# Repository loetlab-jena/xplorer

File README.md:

xplorer
=======

Software for the balloon project "XPlorer 25"

fmmod
======

complex frequency modulator for i/q signal processing

Usage: fmmod inputfile outputfile [carrier] [freqdev] [gain]

             inputfile: path to input file(needs to be single channel)
             outputfile: path to output file
             carrier: carrier frequency in Hz(standard: 0.0)
             freqdev: frequency deviation in Hz(standard: 3000)
             gain: factor for amplification of modulated signal(0.0 < gain < 1.0)

command for compiling:

make fmmod

missionctl
==========

connects the various modules to implement the actual mission schedule. it takes pictures from the camera, 
converts them to the format used by sstv, generates the SSTV and APRS signals, controls the release etc

transmitter
===========

implements a workqueue on the raspberry pi for files to send. with this logic, missionctl doesn't have to keep track
on transmitting files but instead just tells the workqueue to send a file as soon as the RF is free

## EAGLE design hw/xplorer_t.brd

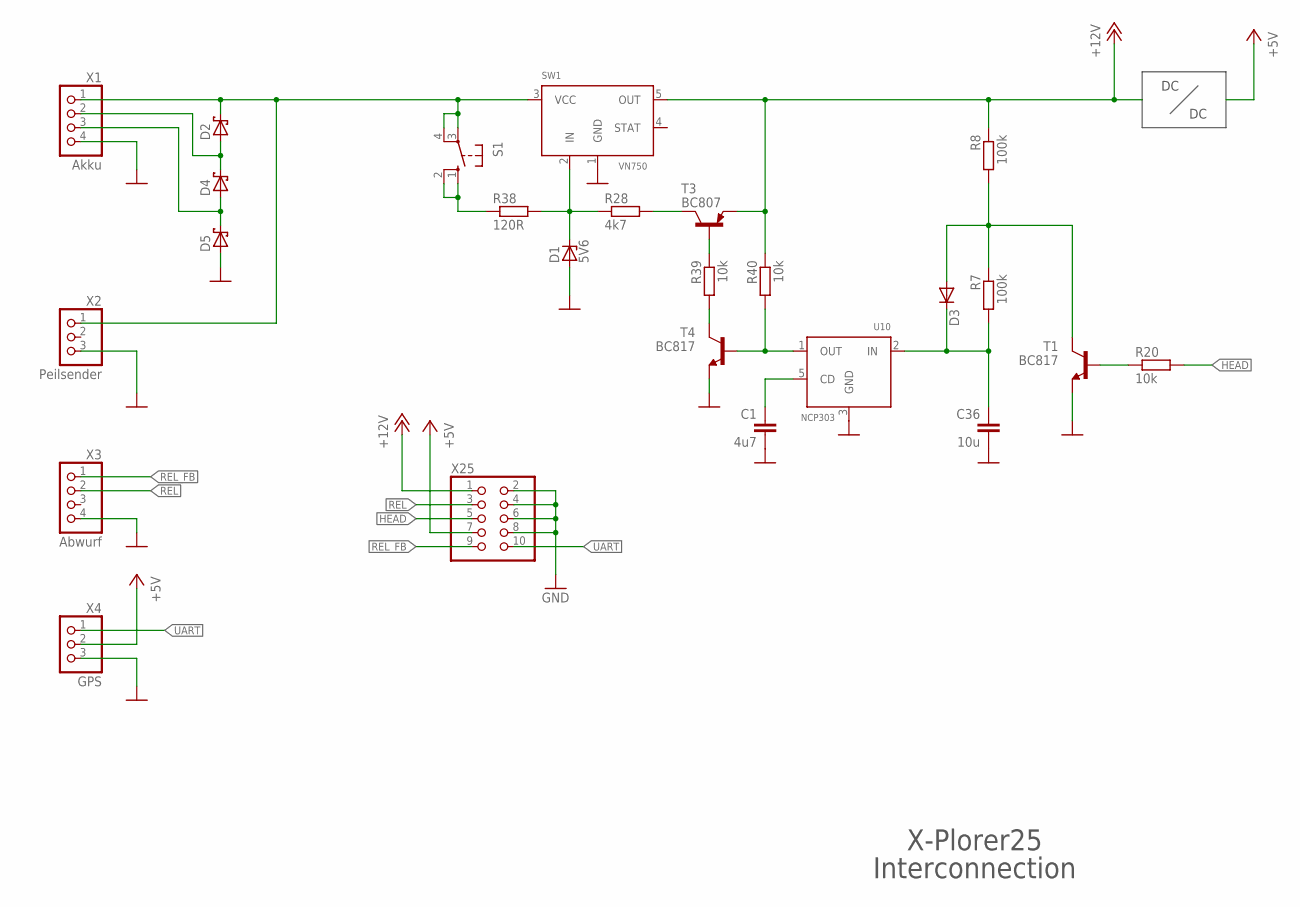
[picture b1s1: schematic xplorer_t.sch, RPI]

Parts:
C1: 4u7; C1210
C36: 10u; C1210
D1: 5V6; SOT23
D2, D4, D5: MBRS130LT3; SMB
D3: DIODE-MINIMELF; MINIMELF
R7, R8: 100k; R0805
R20, R39, R40: 10k; R0805
R28: 4k7; R0805
R38: 120R; R1206
S1: 10-XX; B3F-10XX
SW1: VN750; DDPAK
T1, T4: BC817; SOT23-BEC
T3: BC807; SOT23-BEC
U10: NCP303; SOT23-DBV
X1: Akku; 1X04
X2: Peilsender; 1X03/90
X3: Abwurf; 1X04/90
X4: GPS; 1X03
X25: PINHD-2X5; 2X05

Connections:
+5V: X4.2, X25.7
+12V: R8.1, R40.1, SW1.5 (OUT), T3.E, X25.1
GND: C1.2, C36.2, D1.1 (A), D5.A, SW1.1 (GND), T1.E, T4.E, U10.3 (GND), X1.4, X2.3, X3.4, X4.3, X25.2, X25.4, X25.6, X25.8
HEAD: R20.2, X25.5
unnamed: C1.1, U10.5 (CD)
unnamed: D2.A, D4.C, X1.2
unnamed: D4.A, D5.C, X1.3
unnamed: R38.1, S1.1 (S), S1.2 (S1)
unnamed: C36.1, D3.C, R7.2, U10.2 (IN)
unnamed: D2.C, S1.3, S1.4 (P1), SW1.3 (VCC), X1.1, X2.1
unnamed: D1.3 (C), R28.1, R38.2, SW1.2 (IN)
unnamed: D3.A, R7.1, R8.2, T1.C
unnamed: R28.2, T3.C
unnamed: R20.1, T1.B
unnamed: R39.2, T4.C
unnamed: R39.1, T3.B
unnamed: R40.2, T4.B, U10.1 (OUT)
REL: X3.2, X25.3
REL_FB: X3.1, X25.9
UART: X4.1, X25.10

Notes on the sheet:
X-Plorer25
Interconnection

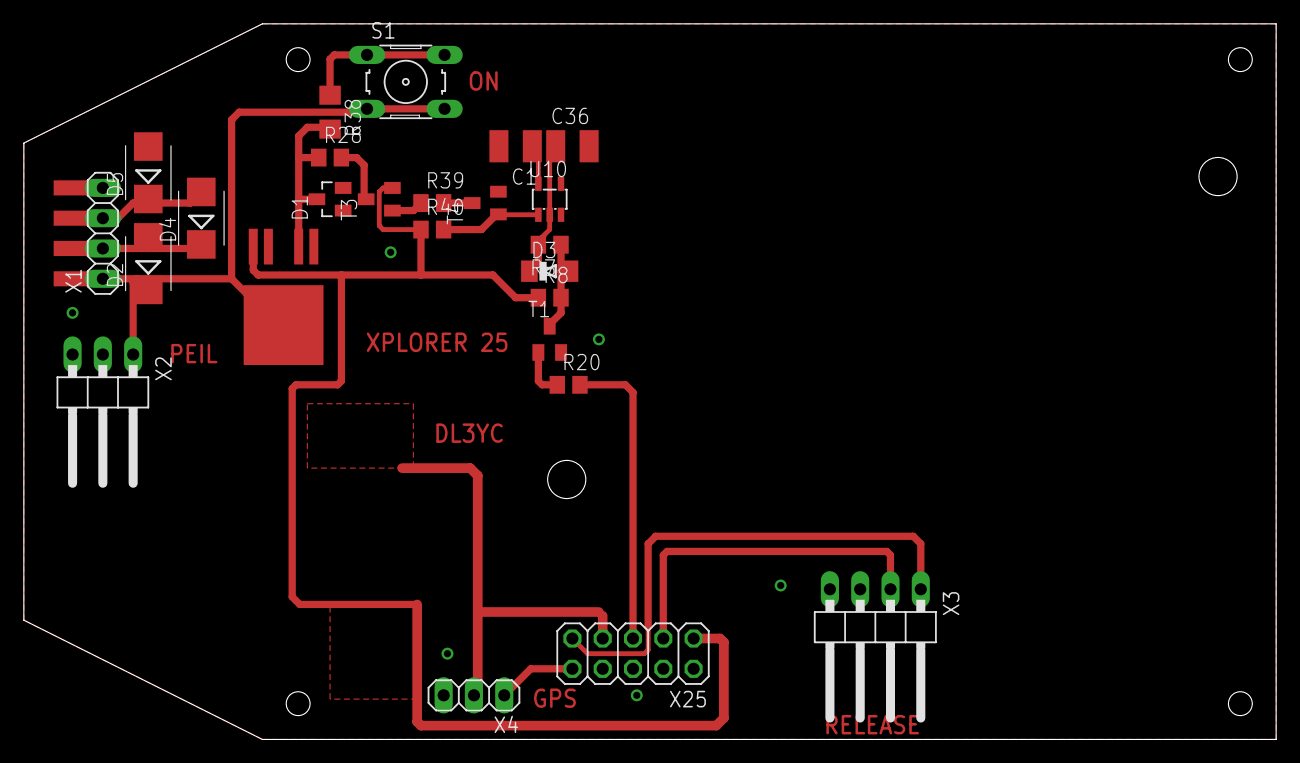
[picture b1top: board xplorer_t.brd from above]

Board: 2 copper layers, 105.0 x 60.0 mm, 25 parts (0 on the bottom side), 20 nets.

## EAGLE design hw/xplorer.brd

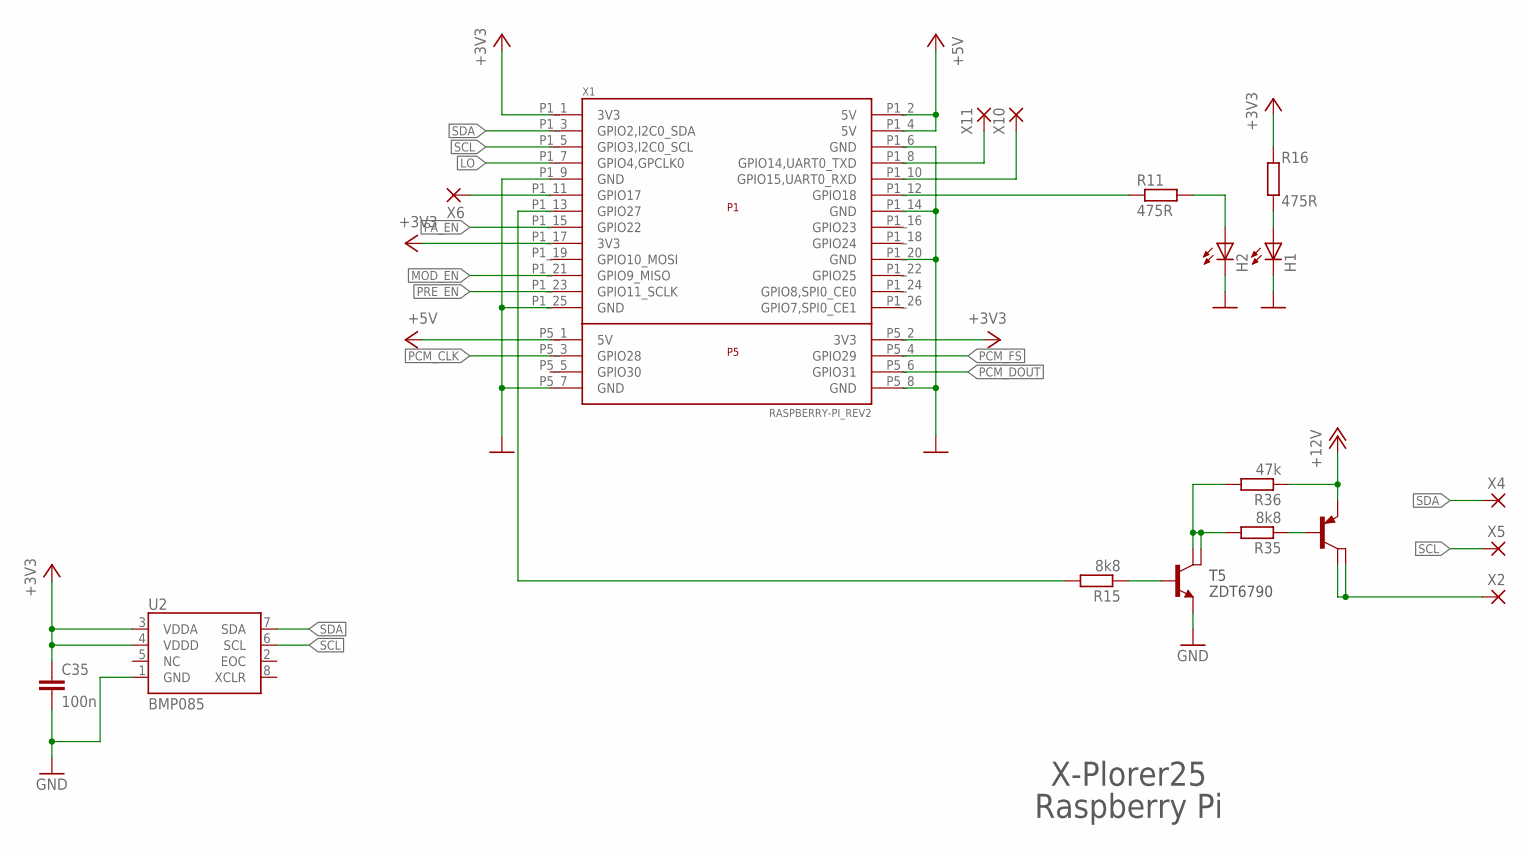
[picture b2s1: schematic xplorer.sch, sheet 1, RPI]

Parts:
C35: 100n; 0603
H1, H2: LEDCHIPLED_0603; CHIPLED_0603
R11, R16: 475R; R0402
R15, R35: 8k8; R0603
R36: 47k; R0603
T5: ZDT6790; SOT223-8
U2: BMP085
X1: RASPBERRY-PI_REV2
X2, X4, X5, X6, X10, X11: SMD2; SMD1,27-2,54

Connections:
$234567898765: T5.3 (C1), T5.4 (C2), X2.1
+3V3: C35.1, R16.2, U2.3 (VDDA), U2.4 (VDDD), X1.P1_1 (3V3), X1.P1_17 (3V3), X1.P5_2 (3V3)
+5V: X1.P1_2 (5V), X1.P1_4 (5V), X1.P5_1 (5V); also elsewhere on the board
+12V: R36.1, T5.5 (E); also elsewhere on the board
GND: C35.2, H1.C, H2.C, T5.7 (E), U2.1 (GND), X1.P1_6 (GND), X1.P1_9 (GND), X1.P1_14 (GND), X1.P1_20 (GND), X1.P1_25 (GND), X1.P5_7 (GND), X1.P5_8 (GND); also elsewhere on the board
LO: X1.P1_7 (GPIO4,GPCLK0); also elsewhere on the board
MOD_EN: X1.P1_21 (GPIO9_MISO); also elsewhere on the board
unnamed: H2.A, R11.2
unnamed: H1.A, R16.1
unnamed: X1.P1_10 (GPIO15,UART0_RXD), X10.1
unnamed: R11.1, X1.P1_12 (GPIO18)
unnamed: R15.1, T5.8 (B)
unnamed: R35.2, R36.2, T5.1 (C1), T5.2 (C2)
unnamed: R35.1, T5.6 (B)
unnamed: X1.P1_8 (GPIO14,UART0_TXD), X11.1
unnamed: R15.2, X1.P1_13 (GPIO27)
PA_EN: X1.P1_15 (GPIO22); also elsewhere on the board
PCM_CLK: X1.P5_3 (GPIO28); also elsewhere on the board
PCM_DOUT: X1.P5_6 (GPIO31); also elsewhere on the board
PCM_FS: X1.P5_4 (GPIO29); also elsewhere on the board
PRE_EN: X1.P1_23 (GPIO11_SCLK); also elsewhere on the board
REL_FB: X1.P1_11 (GPIO17), X6.1
SCL: U2.6 (SCL), X1.P1_5 (GPIO3,I2C0_SCL), X5.1
SDA: U2.7 (SDA), X1.P1_3 (GPIO2,I2C0_SDA), X4.1

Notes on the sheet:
X-Plorer25
Raspberry Pi
ZDT6790

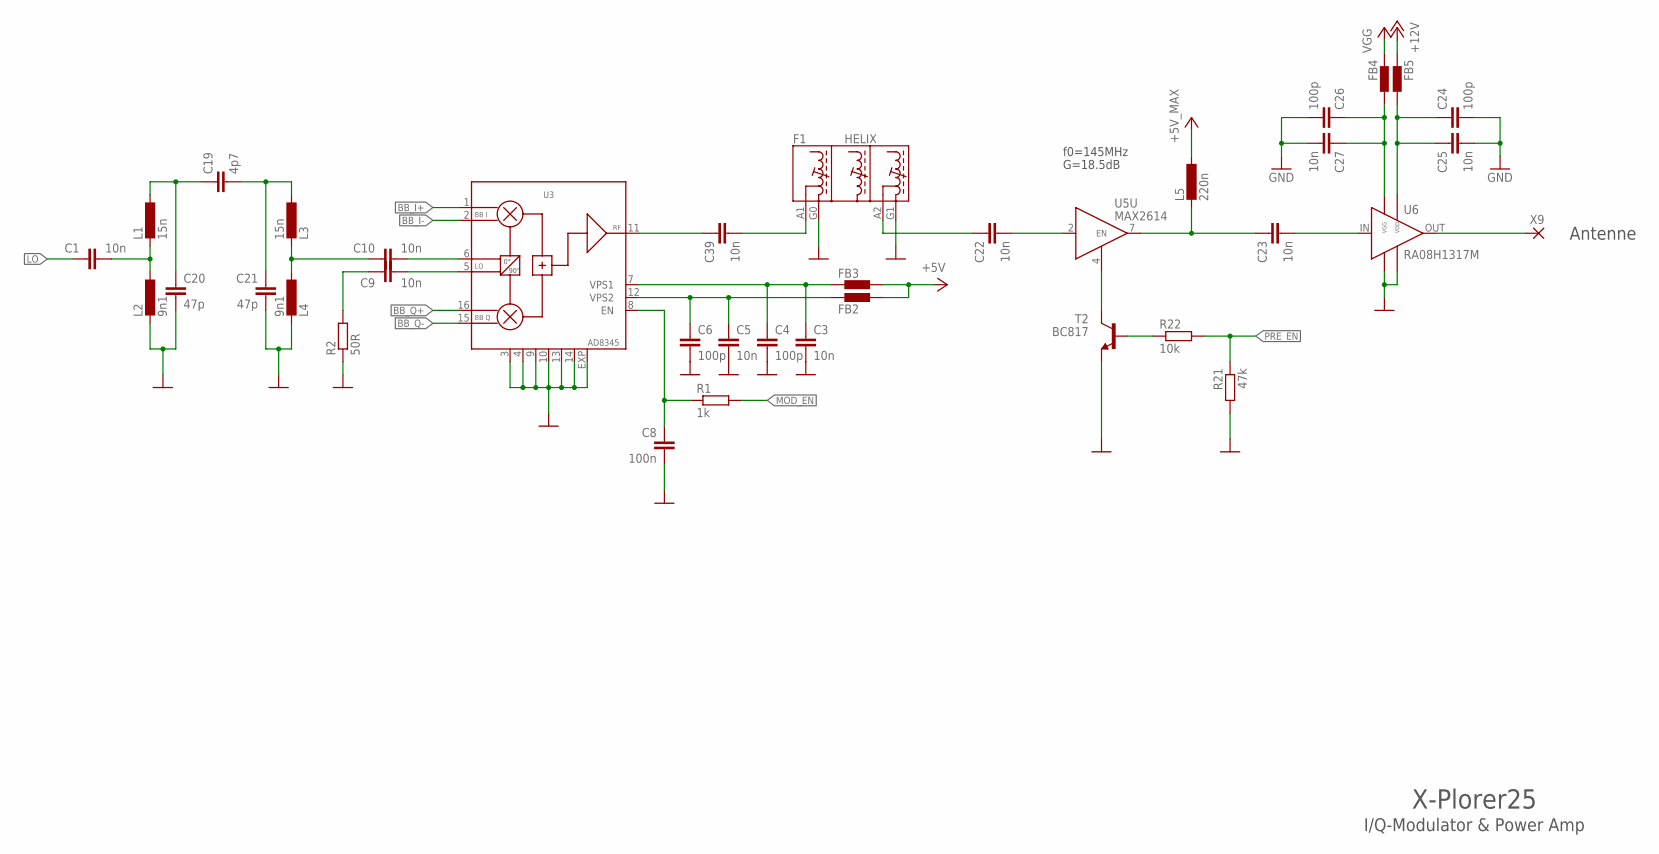
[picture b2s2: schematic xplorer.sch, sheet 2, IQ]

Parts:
C1, C3, C5, C9, C10, C22, C23, C25, C27, C39: 10n; C0603
C4, C6, C24, C26: 100p; C0603
C8: 100n; C0603
C19: 4p7; C0603
C20, C21: 47p; C1812
F1: HELIX; CBT13
FB2, FB3, FB4, FB5: BML15H; R0603
L1, L3: 15n; L2012C
L2, L4: 9n1; L2012C
L5: 220n; L2012C
R1: 1k; R0603
R2: 50R; R0603
R21: 47k; R0603
R22: 10k; R0603
T2: BC817; SOT23-BEC
U3: AD8345; TSSOP16EXP
U5: MAX2614; TDFN8-2X3MM
U6: RA08H1317M
X9: SMD2; SMD1,27-2,54

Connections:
+5V: FB2.2, FB3.2; also elsewhere on the board
+5V_MAX: L5.1; also elsewhere on the board
+12V: FB5.1; also elsewhere on the board
BB_I+: U3.1 (BB_I); also elsewhere on the board
BB_I-: U3.2 (!BB_I); also elsewhere on the board
BB_Q+: U3.16 (BB_Q); also elsewhere on the board
BB_Q-: U3.15 (!BB_Q); also elsewhere on the board
CLEAN_LO: C10.1, L3.2, L4.1
GND: C3.2, C4.2, C5.2, C6.2, C8.2, C20.2, C21.2, C24.2, C25.2, C26.2, C27.2, F1.G0 (GND), F1.G1 (GND), L2.2, L4.2, R2.1, R21.2, T2.E, U3.3 (GND), U3.4 (GND), U3.9 (GND), U3.10 (GND), U3.13 (GND), U3.14 (GND), U3.EXP (GND), U6.G1 (GND), U6.G2 (GND); also elsewhere on the board
LO: C1.1; also elsewhere on the board
MOD_EN: R1.2; also elsewhere on the board
unnamed: C39.2, F1.A1
unnamed: C10.2, U3.6 (LO)
unnamed: C3.1, C4.1, FB3.1, U3.7 (VPS1)
unnamed: C5.1, C6.1, FB2.1, U3.12 (VPS2)
unnamed: C8.1, R1.1, U3.8 (EN)
unnamed: C9.2, U3.5 (!LO)
unnamed: C9.1, R2.2
unnamed: C39.1, U3.11 (RF)
unnamed: C19.2, C21.1, L3.1
unnamed: C22.1, F1.A2
unnamed: C1.2, L1.2, L2.1
unnamed: C19.1, C20.1, L1.1
unnamed: C22.2, U5.2 (IN)
unnamed: C23.1, L5.2, U5.7 (OUT)
unnamed: C23.2, U6.IN
unnamed: C24.1, C25.1, FB5.2, U6.VDD
unnamed: C26.1, C27.1, FB4.2, U6.VGG
unnamed: U6.OUT, X9.1
unnamed: T2.C, U5.4 (EN)
unnamed: R22.1, T2.B
PRE_EN: R21.1, R22.2; also elsewhere on the board
VGG: FB4.1; also elsewhere on the board

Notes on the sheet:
X-Plorer25
I/Q-Modulator & Power Amp
f0=145MHz
G=18.5dB
Antenne

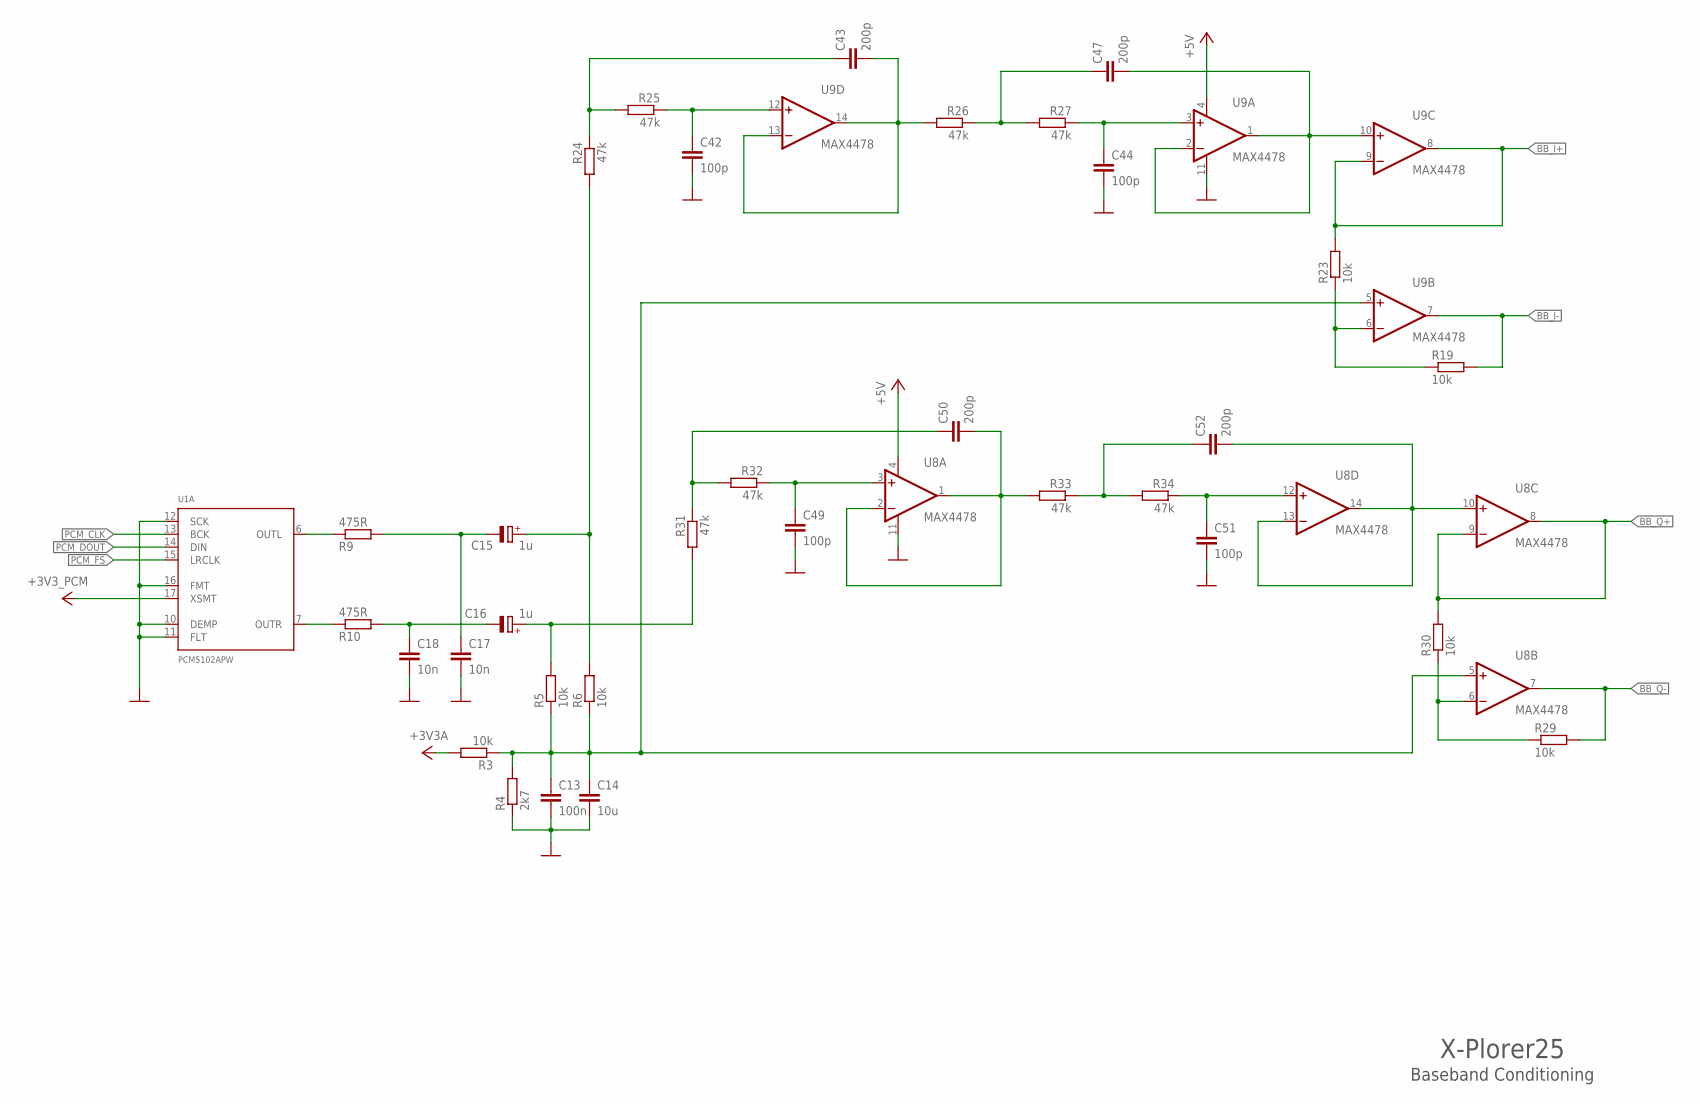
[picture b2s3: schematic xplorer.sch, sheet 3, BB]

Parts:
C13: 100n; C0603
C14: 10u; C0603
C15, C16: 1u; CT3528
C17, C18: 10n; C0603
C42, C44, C49, C51: 100p; C0603
C43, C47, C50, C52: 200p; C0805
R3, R5, R6, R19, R23, R29, R30: 10k; R0603
R4: 2k7; R0603
R9, R10: 475R; R0603
R24, R25, R26, R27, R31, R32, R33, R34: 47k; R0603
U1: PCM5102APW; PW_R-PDSO-G20
U8: MAX4478; SO14; MPN OPA4132UA
U9: MAX4478; SO14

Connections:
$2345: C16.+, R5.2, R31.2
$123456: C15.+, R6.2, R24.2
+3V3A: R3.2; also elsewhere on the board
+3V3_PCM: U1.17 (XSMT); also elsewhere on the board
+5V: U8.4 (V+), U9.4 (V+); also elsewhere on the board
BB_I+: R23.2, U9.8 (OUT), U9.9 (-IN); also elsewhere on the board
BB_I-: R19.2, U9.7 (OUT); also elsewhere on the board
BB_Q+: R30.2, U8.8 (OUT), U8.9 (-IN); also elsewhere on the board
BB_Q-: R29.2, U8.7 (OUT); also elsewhere on the board
GND: C13.2, C14.2, C17.2, C18.2, C42.2, C44.2, C49.2, C51.2, R4.1, U1.10 (DEMP), U1.11 (FLT), U1.12 (SCK), U1.16 (FMT), U8.11 (V-), U9.11 (V-); also elsewhere on the board
unnamed: C49.1, R32.1, U8.3 (+IN)
unnamed: R10.1, U1.7 (OUTR)
unnamed: C16.-, C18.1, R10.2
unnamed: R9.1, U1.6 (OUTL)
unnamed: C50.1, R31.1, R32.2
unnamed: C52.2, U8.10 (+IN), U8.13 (-IN), U8.14 (OUT)
unnamed: C51.1, R34.1, U8.12 (+IN)
unnamed: C52.1, R33.1, R34.2
unnamed: C42.1, R25.1, U9.12 (+IN)
unnamed: C43.1, R24.1, R25.2
unnamed: C47.2, U9.1 (OUT), U9.2 (-IN), U9.10 (+IN)
unnamed: C44.1, R27.1, U9.3 (+IN)
unnamed: C47.1, R26.1, R27.2
unnamed: C43.2, R26.2, U9.13 (-IN), U9.14 (OUT)
unnamed: C50.2, R33.2, U8.1 (OUT), U8.2 (-IN)
unnamed: R19.1, R23.1, U9.6 (-IN)
unnamed: R29.1, R30.1, U8.6 (-IN)
unnamed: C15.-, C17.1, R9.2
PCM_CLK: U1.13 (BCK); also elsewhere on the board
PCM_DOUT: U1.14 (DIN); also elsewhere on the board
PCM_FS: U1.15 (LRCLK); also elsewhere on the board
VGND: C13.1, C14.1, R3.1, R4.2, R5.1, R6.1, U8.5 (+IN), U9.5 (+IN)

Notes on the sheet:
X-Plorer25
Baseband Conditioning

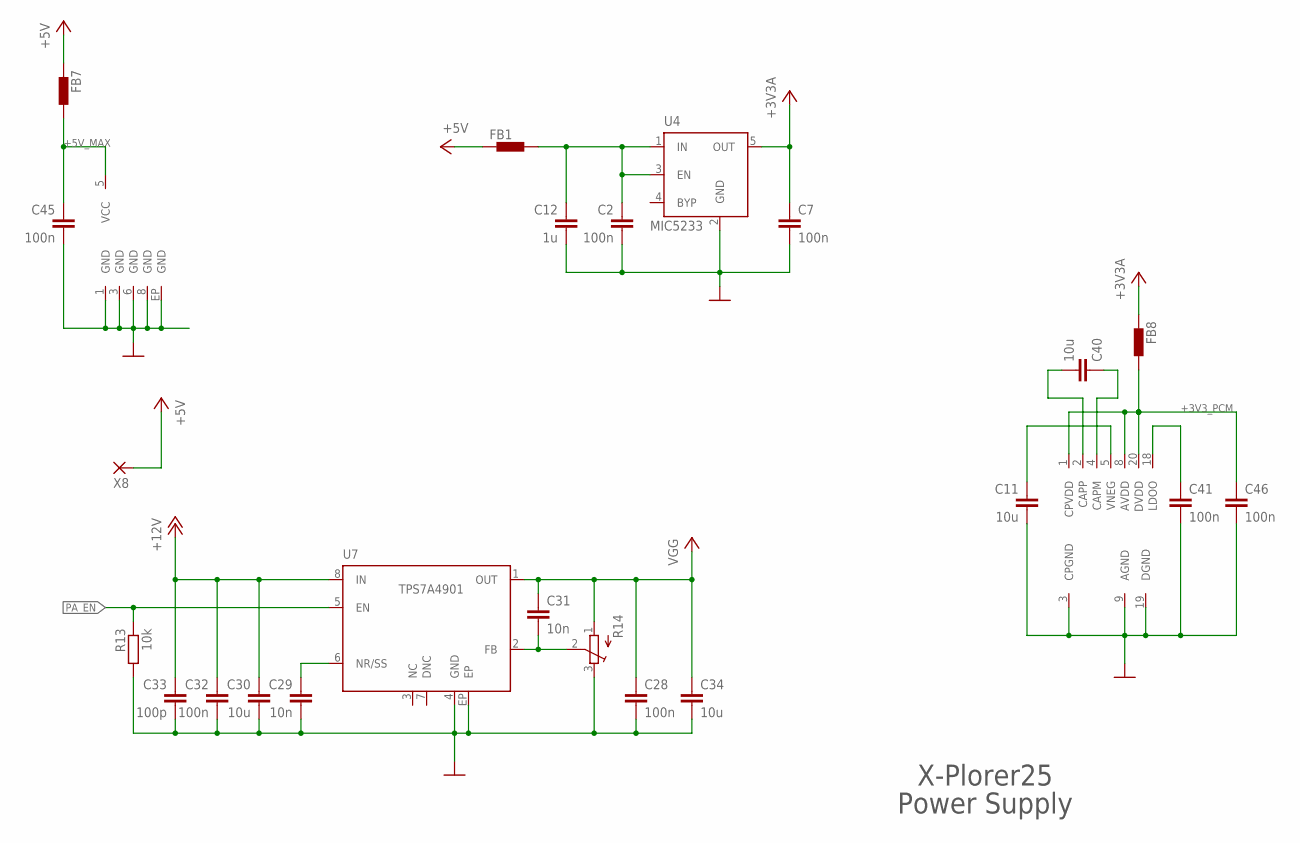
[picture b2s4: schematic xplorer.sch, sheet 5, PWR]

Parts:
C2, C7, C28, C32, C41, C45, C46: 100n; C0603
C11, C40: 10u; C0603
C12: 1u; C0603
C29: 10n; C0603K
C30, C34: 10u; C0805
C31: 10n; C0603
C33: 100p; C0603
FB1, FB7, FB8: BML15H; R0603
R13: 10k; R0603
R14: TRIM_EU-SM-42/43X; SM-42/43X
U1: PCM5102APW; PW_R-PDSO-G20
U4: MIC5233; SOT23-5
U5: MAX2614; TDFN8-2X3MM
U7: TPS7A4901; PW_R-PDSO-G08
X8: SMD2; SMD1,27-2,54

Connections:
12V_F: C2.1, C12.1, FB1.2, U4.1 (IN), U4.3 (EN)
+3V3A: C7.1, FB8.1, U4.5 (OUT); also elsewhere on the board
+3V3_PCM: C46.1, FB8.2, U1.1 (CPVDD), U1.8 (AVDD), U1.20 (DVDD); also elsewhere on the board
+5V: FB1.1, FB7.1, X8.1; also elsewhere on the board
+5V_MAX: C45.1, FB7.2, U5.5 (VCC); also elsewhere on the board
+12V: C30.1, C32.1, C33.1, U7.8 (IN); also elsewhere on the board
GND: C2.2, C7.2, C11.2, C12.2, C28.2, C29.2, C30.2, C32.2, C33.2, C34.2, C41.2, C45.2, C46.2, R13.2, R14.3 (E), U1.3 (CPGND), U1.9 (AGND), U1.19 (DGND), U4.2 (GND), U5.1 (GND), U5.3 (GND), U5.6 (GND), U5.8 (GND), U5.EP (GND), U7.4 (GND), U7.EP; also elsewhere on the board
unnamed: C31.2, R14.2 (S), U7.2 (FB)
unnamed: C11.1, U1.5 (VNEG)
unnamed: C40.1, U1.4 (CAPM)
unnamed: C40.2, U1.2 (CAPP)
unnamed: C41.1, U1.18 (LDOO)
unnamed: C29.1, U7.6 (NR/SS)
PA_EN: R13.1, U7.5 (EN); also elsewhere on the board
VGG: C28.1, C31.1, C34.1, R14.1 (A), U7.1 (OUT); also elsewhere on the board

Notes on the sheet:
X-Plorer25
Power Supply

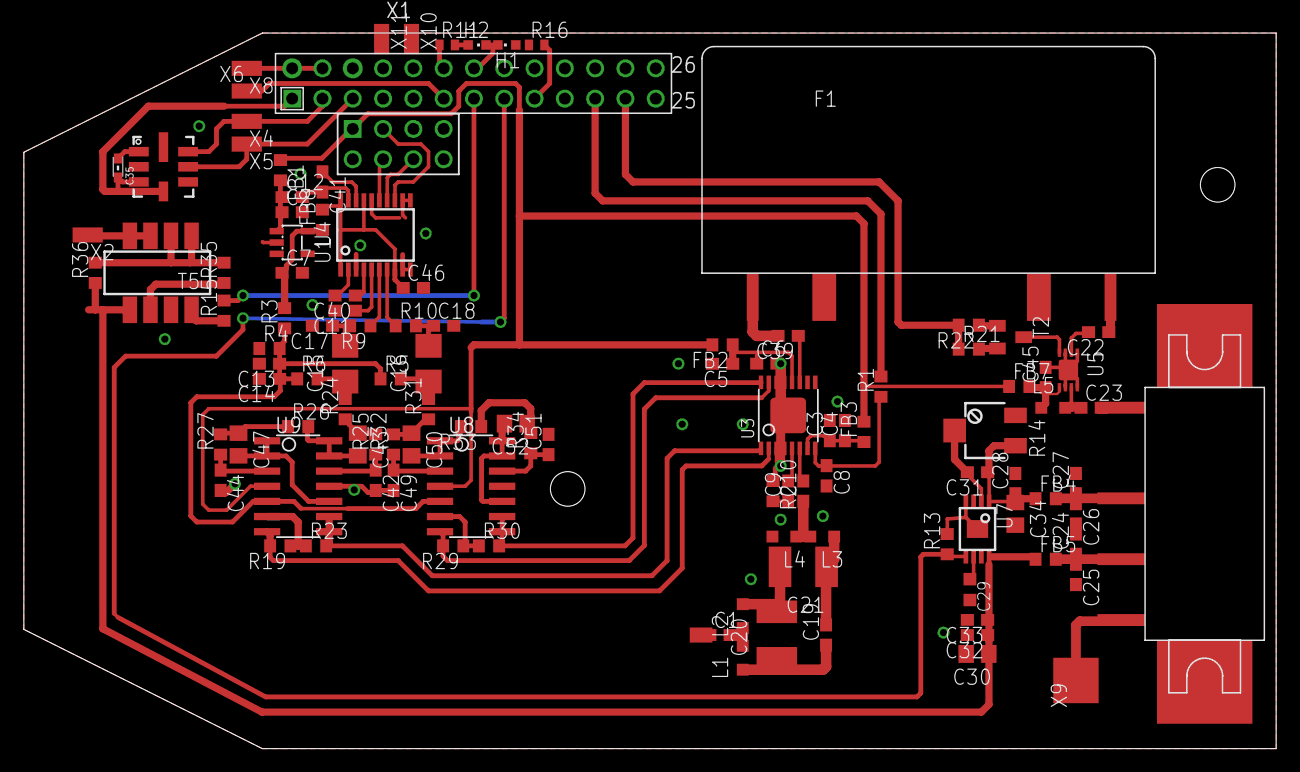
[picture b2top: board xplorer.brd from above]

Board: 2 copper layers, 105.0 x 60.0 mm, 112 parts (0 on the bottom side), 81 nets.

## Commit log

2014-02-17 add fmmod
    fmmod, the IQ FM modulator is added in its first version
2014-02-17 add fmmod gain parameter
    an optional parameter for setting the output volume is added to fmmod
2014-02-17 fix compile error in fmmod
    addition of the gain-parameter lead to a build failure
2014-02-21 Update fmmod.c
    removed date in header
    changed volume to gain in usage
    added description for gain in usage
    range check for gain
    untested.
2014-02-21 error handling of samplerate(nyquist criterion)
    show error when carrier + freqdev >= samplerate/2
2014-02-21 error handling of freqdev
    show error when frequency deviation is negative
2014-02-21 Typo in usage
2014-02-21 Typo in error message
2014-02-21 added fmmod description
2014-02-21 Create robot36.c
    Copied from https://gist.github.com/anonymous/5723053
2014-02-21 Copied Makefile from robot36 repo
2014-02-21 add fmmod compile command
2014-02-21 cleanup
2014-02-21 update compile command for fmmod
2014-02-21 add the python AFSK encoder
    this commit adds the python implementation. it is heavily commented for
    review. has to be recoded in C and highly optimised to be efficient on
    board.
2014-02-21 removed unused paramter
2014-02-21 added parameters for I/Q alignment
    gain and phase parameters to compensate I/Q imbalance
2014-02-21 bugfix on gain and phase parameters
2014-02-22 argument check fix in fmmod
    this fixes the argument range check. it was not possible to include a
    phase offset
2014-02-23 introduce the mission control framework
    adds mission-control and the transmitter module. the transmitter module
    presents a workqueue to the system, handling all the RF lifting
    (frequency setup, enabling/disabling of the PA, I/Q audio playing, etc)
    the missionctl ATM only represents a test utility for transmitter, but
    will in the future implement the actual mission schedule
2014-02-23 introduce python logging framework
    this replaces the "print"-orgys by using the logging feature of python.
    also, adds TODO in the transmitter
2014-02-23 copy from dokuwiki
2014-02-23 intendation fix in log output
    simple one-line fix for bad intendation
2014-02-23 first step for an effective implementation
    new structure, command line parameters..
2014-02-23 Rename lo_ctl to lo_ctl.c
2014-02-23 fix compile error
2014-02-23 fix string compare
2014-02-23 add loctl
2014-02-23 Rename lo_ctl.c to loctl.c
2014-02-23 add gps listener, switch to python2.7
    this commit adds the GPS listener and switches everything back to
    python2.7, which is no big drawback. it's just because the
    GPSd-python-bindings are not available under python3
2014-02-23 fix the all-target and the fmmod-target in Makefile
    all-target was broken and loctl-target had syntax error
2014-02-24 corrected typo
    ($BIN) vs $(BIN)
2014-02-24 fix freqdev parameter error
    freqdev was only set if it was the last argument given. this was not
    intended.
2014-02-24 add raspberry-pi relevant parts
    this adds functionality for running on the raspberry pi. it
    conditionally includes the GPIO module and opts out all GPIO commands if
    we're not running on raspberry pi.
    also removes some old code, and waits for the gps-listener to have a fix
2014-02-24 add the install instructions
    this adds install instructions, what do to after setting up a blank
    raspian image
    this is far from complete, please review and add
2014-02-25 add gpio dummy handlers
    when not running on a raspberry pi, the GPIO accesses are opted out and
    only used as debugging messages in the log.
2014-02-25 opt out /dev/mem from loctl when not on arm
2014-02-25 add hfmod module and implement mission flow
    this adds a dummy module that will handle the actual modulation and
    encoding for aprs and sstv, also fmmod.
    it also includes the flow that will be in the mission, including
    parameters for mission time.
    some things still need to be done, they are marked with TODO
2014-02-26 add dummycode to hfmod
2014-02-26 bugfix for loop delays
2014-02-27 add todo in robot36
    we need to be able to give the input and output path of the sstv-image!
2014-02-27 add wav and jpg-files to clean-target
2014-02-27 add the production code to hfmod
    this is untested
2014-02-27 implement lo on/off
2014-02-27 fix the makefile
    used two compile passes up to this point
2014-02-27 rename hfmod to rfmod
    just to stick to language standards
2014-02-27 add input/output filename parameters for robot36
2014-02-27 add logfile deletion to clean-target
    fix runtime errors because of rfmod-rename
2014-02-27 add runtime error because of wrong parameters
2014-02-27 change pin numbers for LEDs
2014-02-27 fix typo in GPIO module
2014-02-27 integrate changes from raspi SD card
2014-02-27 fixes #1 from mission test
2014-02-27 add sounds, fmmoded 5kHz offset, 6kHz dev
2014-03-12 include thursday-changeset from rpi
2014-03-14 fixes for next software test
2014-03-14 implement release, correct LO-offsets, deactivation of RF
2014-03-14 remove obsolete TODOs
2014-03-18 concatenate wav files before transmission
2014-03-20 add pcb files
2014-03-20 include correct GPIO numbers for payload, handle rf on and off
2014-03-20 update sound files, fmmod 0 hz offset
2014-03-20 correct release pin numbers
2014-03-20 revert gpio-state/io-mode changes
2014-03-20 fix output mode setting in transmitter
2014-03-20 reduce volume on the fmmod sounds
2014-03-20 audio processing of wave files
2014-03-20 equalize audio files, 300Hz-3,5kHz
2014-03-20 switch LO on/off, correct queueing of numbers
2014-03-20 replace number 2 with better understandable version
2014-03-26 lower gain to 0.1 for all audio files
2014-03-26 lower the volume even more
2014-04-03 change release feedback polarity
2014-04-17 add remaining fixes for productive tests
2014-04-17 add loctl570
2014-04-17 change fmmod parameters and prepare for 15kHz offset
2014-04-17 add 15kHz offset to modulation of numbers
2014-04-17 add instruction to sync SD-card before headshot
2014-04-17 add start script
2014-04-17 add documentation, set up new raspi system
2014-04-19 add i2c depencies to installation manual
2014-04-19 handle i2c slave not present error in loctl570
2014-04-19 output warning to log if LO could not be set
2014-04-19 format APRS strings properly, use them
2014-04-19 more installing instructions
2014-04-20 use the correct packet file, correct si570 offset (5kHz)
2014-04-20 fix format error in APRS packet
2014-04-20 finally fix APRS data format
2014-04-20 add wait time after warning signal
2014-04-20 switch frequencies 144.800/145.200
2014-04-20 remove main from afskencoder
2014-04-20 dirty hack: convert DD to DMS coordinates
2014-04-20 convert meter to feet
2014-04-21 clean up APRS packet generator
2014-04-21 disable GPIO checking for release, increase time
2014-04-21 rev2 of rf board
2014-04-21 correct pcb file structure
2014-04-24 add board files of upper pcb with headshot, switching supply and connectors
2014-04-26 change pinout for new hardware revision
2014-04-30 install instructions reformat
2014-05-02 add cron file for camera images
2014-05-02 quote directory name
2014-05-02 remove 180deg rotation from sstv picture
2014-05-02 make camcron executable
2014-05-02 clarify installation instructions
2014-05-02 fix callsign and symbol in APRS
2014-05-02 aprs symbol fix
2014-05-02 set default mission length to 20min, 20min, 20min
2014-05-02 add hack for frequency offsets of SI570
2014-05-02 fix the hack, typo
2014-05-02 add debug output to SI570-hack
2014-05-02 fix the MAC-address
2014-05-03 improve error handling
    we found crashed with the new GPS mouse, seemingly because GPSd provides
    different values than with the HOLUX mouse when there is no fix
    available
2014-05-03 fix the MAC-adress-tests
2014-05-03 MAC address string check
2014-05-03 log all unhandled exceptions to log file
2014-05-03 release payload on unhandled exception
2014-05-03 add exception output to afskencoder
2014-05-04 add warning to aprs string conversion
2014-05-04 add new warning siren
2014-05-05 fix error in debug output
2014-05-06 handle timeout for raspistill, log timeout error
2014-05-06 add verbose log to start script
2014-05-19 updated install instructions

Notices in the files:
parts and their libraries:
SparkFun: Licensing: CC v3.0 Share-Alike You are welcome to use this library for commercial purposes.
